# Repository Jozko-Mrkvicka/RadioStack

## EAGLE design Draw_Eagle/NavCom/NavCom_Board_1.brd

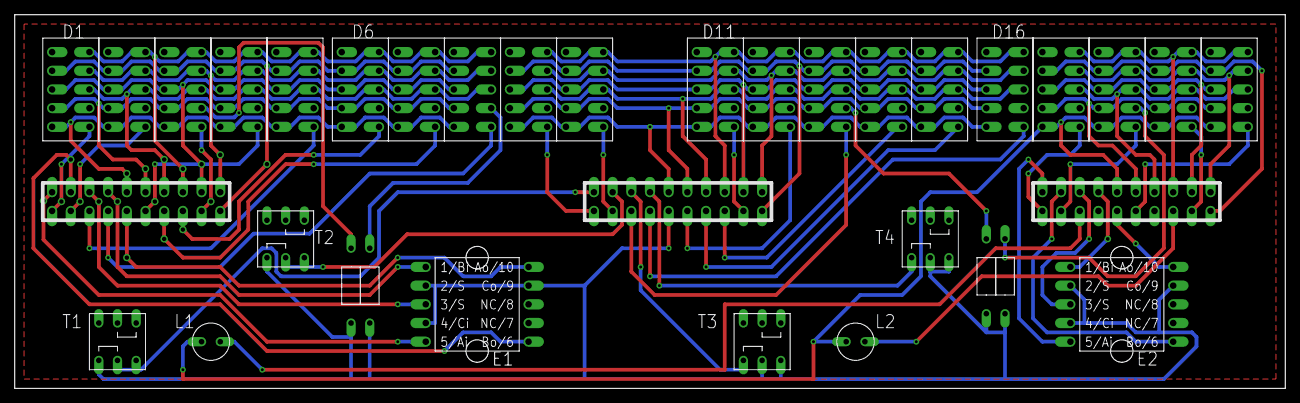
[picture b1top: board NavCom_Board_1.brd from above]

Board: 2 copper layers, 172.7 x 50.8 mm, 35 parts (0 on the bottom side), 62 nets.

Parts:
D1, D2, D3, D4, D5, D6, D7, D8, D9, D10, D11, D12, D13, D14, D15, D16, D17, D18, D19, D20: SA3611EWA
E37#1, E37#2: ELMA_E37
KON4, KON5, KON6: LISTA_2X10
LED1, LED2: LED_5MM
T1, T2, T3, T4: P1-0S
U$1, U$2, U$3, U$4: REZISTOR

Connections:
D1: D1.6, KON4.1
D2: D2.6, KON4.2
D3: D3.6, KON4.9
D4: D4.6, KON4.6
D5: D5.6, KON4.3
D6: D6.6, KON4.8
D7: D7.6, KON4.7
D8: D8.6, KON4.4
D9: D9.6, KON5.1
D10: D10.6, KON5.2
D11: D11.6, KON5.9
D12: D12.6, KON5.6
D13: D13.6, KON5.3
D14: D14.6, KON5.8
D15: D15.6, KON5.7
D16: D16.6, KON5.4
D17: D17.6, KON6.1
D18: D18.6, KON6.2
D19: D19.6, KON6.9
D20: D20.6, KON6.6
DRIVER1_SEG2: D1.2, D2.2, D3.2, D4.2, D5.2, D6.2, D7.2, D8.2, KON4.10
DRIVER1_SEG3: D1.3, D2.3, D3.3, D4.3, D5.3, D6.3, D7.3, D8.3, KON4.12
DRIVER1_SEG4: D1.4, D2.4, D3.4, D4.4, D5.4, D6.4, D7.4, D8.4, KON4.15
DRIVER1_SEG5: D1.5, D2.5, D3.5, D4.5, D5.5, D6.5, D7.5, D8.5, KON4.16
DRIVER1_SEG8: D1.8, D2.8, D3.8, D4.8, D5.8, D6.8, D7.8, D8.8, KON4.14
DRIVER1_SEG9: D1.9, D2.9, D3.9, D4.9, D5.9, D6.9, D7.9, D8.9, KON4.11
DRIVER1_SEG10: D1.10, D2.10, D3.10, D4.10, D5.10, D6.10, D7.10, D8.10, KON4.13
DRIVER2_SEG2: D9.2, D10.2, D11.2, D12.2, D13.2, D14.2, D15.2, D16.2, KON5.10
DRIVER2_SEG3: D9.3, D10.3, D11.3, D12.3, D13.3, D14.3, D15.3, D16.3, KON5.12
DRIVER2_SEG4: D9.4, D10.4, D11.4, D12.4, D13.4, D14.4, D15.4, D16.4, KON5.15
DRIVER2_SEG5: D9.5, D10.5, D11.5, D12.5, D13.5, D14.5, D15.5, D16.5, KON5.16
DRIVER2_SEG8: D9.8, D10.8, D11.8, D12.8, D13.8, D14.8, D15.8, D16.8, KON5.14
DRIVER2_SEG9: D9.9, D10.9, D11.9, D12.9, D13.9, D14.9, D15.9, D16.9, KON5.11
DRIVER2_SEG10: D9.10, D10.10, D11.10, D12.10, D13.10, D14.10, D15.10, D16.10, KON5.13
DRIVER3_SEG2: D17.2, D18.2, D19.2, D20.2, KON6.10
DRIVER3_SEG3: D17.3, D18.3, D19.3, D20.3, KON6.12
DRIVER3_SEG4: D17.4, D18.4, D19.4, D20.4, KON6.15
DRIVER3_SEG5: D17.5, D18.5, D19.5, D20.5, KON6.16, LED1.P$2, LED2.P$2
DRIVER3_SEG8: D17.8, D18.8, D19.8, D20.8, KON6.14
DRIVER3_SEG9: D17.9, D18.9, D19.9, D20.9, KON6.11
DRIVER3_SEG10: D17.10, D18.10, D19.10, D20.10, KON6.13
E37#1_1: E37#1.1, KON4.17
E37#1_3: E37#1.3, KON4.18
E37#1_5: E37#1.5, KON4.20
E37#1_6: E37#1.6, KON4.19
E37#1_10: E37#1.10, KON4.5
E37#2_1: E37#2.1, KON6.17
E37#2_3: E37#2.3, KON6.18
E37#2_5: E37#2.5, KON6.20
E37#2_6: E37#2.6, KON6.19
E37#2_10: E37#2.10, KON6.5
GND: E37#1.2, E37#1.4, E37#1.9, E37#2.2, E37#2.4, E37#2.9, KON5.5, T1.4, T2.4, T3.5, T3.6, T4.5, T4.6, U$1.P$1, U$2.P$1, U$3.P$1, U$4.P$1
LED1: KON6.3, LED1.P$1
LED2: KON6.8, LED2.P$1
unnamed: D3.7, U$4.P$2
unnamed: D18.7, U$2.P$2
unnamed: D13.7, U$1.P$2
unnamed: D8.7, U$3.P$2
T1: KON5.20, T1.5, T1.6
T2: KON5.19, T2.5, T2.6
T3: KON5.18, T3.4
T4: KON5.17, T4.4

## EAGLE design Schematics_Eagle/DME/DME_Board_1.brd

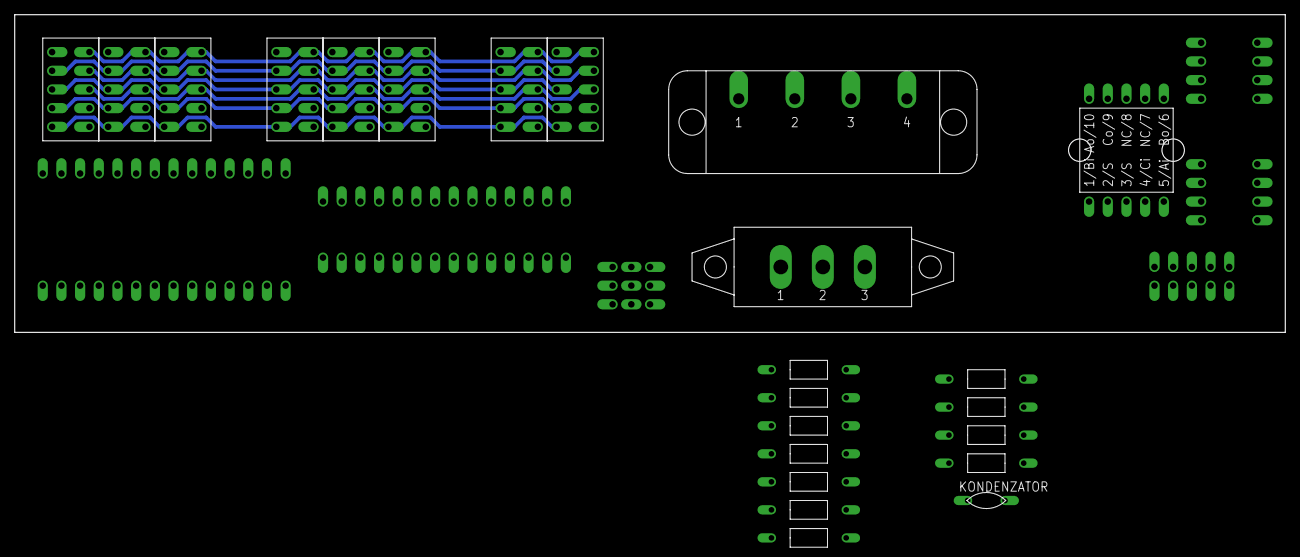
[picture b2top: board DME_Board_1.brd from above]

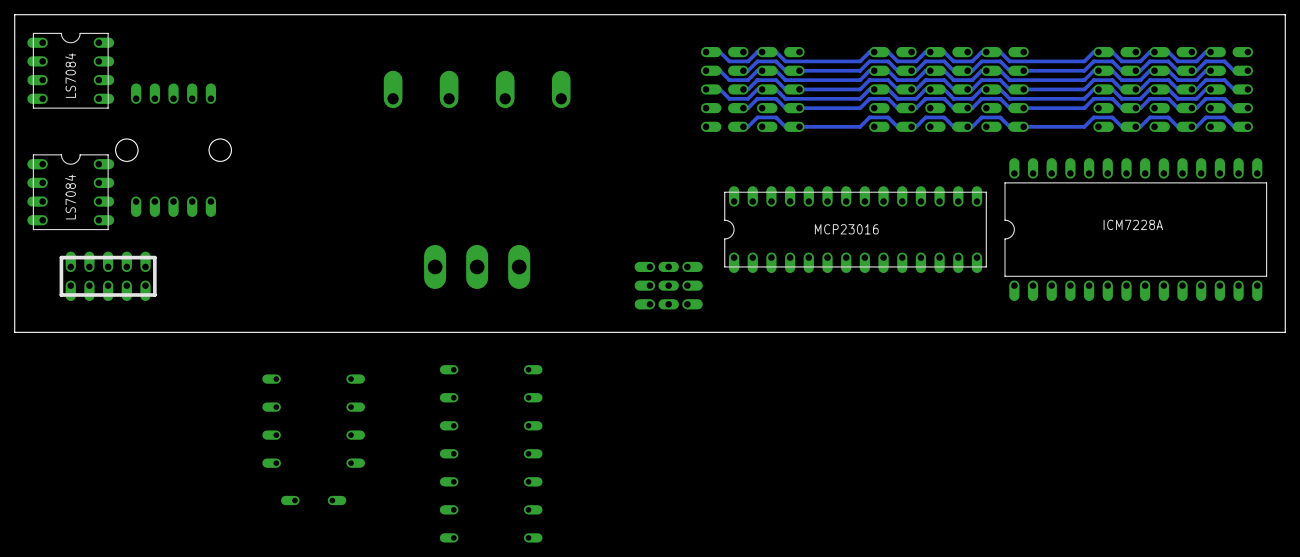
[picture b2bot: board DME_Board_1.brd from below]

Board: 2 copper layers, 172.7 x 43.2 mm, 29 parts (5 on the bottom side), 7 nets.

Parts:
U$1, U$2, U$3, U$4, U$5, U$6, U$7, U$8: SA3611EWA
U$9: ELMA_E37
U$10: 46311LD
U$11, U$13, U$15, U$19, U$25, U$26, U$27, U$28, U$29, U$30, U$31: REZISTOR
U$12: T220
U$14: ICM7228A
U$16: MCP23016
U$17: LISTA_2X5
U$21, U$22: LS7084
U$23: KONDENZATOR
U$24: ADRESA_0..2

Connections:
unnamed: U$1.10, U$2.10, U$3.10, U$4.10, U$5.10, U$6.10, U$7.10, U$8.10
unnamed: U$1.9, U$2.9, U$3.9, U$4.9, U$5.9, U$6.9, U$7.9, U$8.9
unnamed: U$1.8, U$2.8, U$3.8, U$4.8, U$5.8, U$6.8, U$7.8, U$8.8
unnamed: U$1.5, U$2.5, U$3.5, U$4.5, U$5.5, U$6.5, U$7.5, U$8.5
unnamed: U$1.2, U$2.2, U$3.2, U$4.2, U$5.2, U$6.2, U$7.2, U$8.2
unnamed: U$1.3, U$2.3, U$3.3, U$4.3, U$5.3, U$6.3, U$7.3, U$8.3
unnamed: U$1.4, U$2.4, U$3.4, U$4.4, U$5.4, U$6.4, U$7.4, U$8.4

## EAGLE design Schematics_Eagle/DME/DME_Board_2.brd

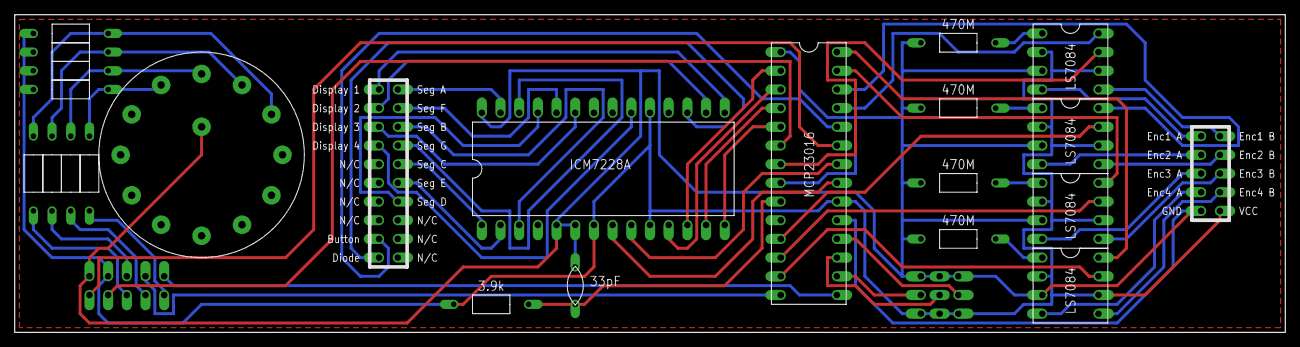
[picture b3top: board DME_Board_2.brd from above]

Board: 2 copper layers, 172.7 x 43.2 mm, 25 parts (1 on the bottom side), 57 nets.

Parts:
U$1, U$2, U$3, U$4: LS7084
U$5, U$27: LISTA_2X5
U$6: ICM7228A
U$7: LISTA_2X10
U$8, U$10, U$12, U$13: 470M; REZISTOR
U$9: MCP23016
U$11: ADRESA_0..2
U$14: 3.9k; REZISTOR
U$15: 33pF; KONDENZATOR
U$16: ROTARY_SWITCH
U$17, U$18, U$19, U$20, U$21, U$22, U$23, U$24: REZISTOR

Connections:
GND: U$1.P$3, U$2.P$3, U$3.P$3, U$4.P$3, U$5.1, U$6.P$5, U$6.P$6, U$6.P$28, U$8.P$1, U$9.VSS1, U$9.VSS2, U$9.VSS3, U$10.P$1, U$11.P$3, U$11.P$4, U$11.P$9, U$12.P$1, U$13.P$1, U$15.P$2, U$16.A, U$27.5
unnamed: U$6.P$27, U$7.20
unnamed: U$6.P$24, U$7.19
unnamed: U$6.P$3, U$7.18
unnamed: U$6.P$26, U$7.17
unnamed: U$6.P$1, U$7.16
unnamed: U$6.P$2, U$7.15
unnamed: U$6.P$25, U$7.14
unnamed: U$6.P$15, U$7.1
unnamed: U$6.P$16, U$7.2
unnamed: U$6.P$23, U$7.3
unnamed: U$6.P$20, U$7.4
unnamed: U$1.P$2, U$1.P$6, U$2.P$2, U$2.P$6, U$3.P$2, U$3.P$6, U$4.P$2, U$4.P$6, U$5.2, U$6.P$7, U$6.P$10, U$6.P$19, U$9.VDD, U$11.P$1, U$11.P$6, U$11.P$7, U$14.P$1, U$17.P$1, U$18.P$1, U$19.P$1, U$20.P$1, U$27.6
unnamed: U$6.P$12, U$9.GP1.0
unnamed: U$1.P$8, U$9.GP0.4
unnamed: U$2.P$8, U$9.GP0.5
unnamed: U$1.P$1, U$8.P$2
unnamed: U$2.P$1, U$10.P$2
unnamed: U$3.P$1, U$12.P$2
unnamed: U$4.P$1, U$13.P$2
unnamed: U$6.P$11, U$9.GP1.1
unnamed: U$3.P$8, U$9.GP0.6
unnamed: U$4.P$8, U$9.GP0.7
unnamed: U$1.P$7, U$9.GP1.4
unnamed: U$1.P$4, U$27.1
unnamed: U$1.P$5, U$27.10
unnamed: U$2.P$4, U$27.2
unnamed: U$2.P$5, U$27.9
unnamed: U$3.P$4, U$27.3
unnamed: U$3.P$5, U$27.8
unnamed: U$4.P$4, U$27.4
unnamed: U$4.P$5, U$27.7
unnamed: U$2.P$7, U$9.GP1.5
unnamed: U$3.P$7, U$9.GP1.6
unnamed: U$4.P$7, U$9.GP1.7
unnamed: U$9.A0, U$11.P$8
unnamed: U$9.A1, U$11.P$5
unnamed: U$9.A2, U$11.P$2
unnamed: U$6.P$13, U$9.GP1.2
unnamed: U$6.P$14, U$9.GP1.3
unnamed: U$16.11, U$17.P$2, U$21.P$2
unnamed: U$6.P$8, U$9.GP0.0
unnamed: U$6.P$9, U$9.GP0.1
unnamed: U$16.12, U$18.P$2, U$22.P$2
unnamed: U$5.4, U$9.SCL
unnamed: U$5.5, U$9.SDA
unnamed: U$5.9, U$9.~INT
unnamed: U$5.10, U$9.GP0.2
unnamed: U$9.CLK, U$14.P$2, U$15.P$1
unnamed: U$7.9, U$9.GP0.3
unnamed: U$6.P$17, U$7.10
unnamed: U$16.1, U$19.P$2, U$23.P$2
unnamed: U$16.2, U$20.P$2, U$24.P$2
unnamed: U$5.8, U$24.P$1
unnamed: U$5.3, U$23.P$1
unnamed: U$5.7, U$22.P$1
unnamed: U$5.6, U$21.P$1

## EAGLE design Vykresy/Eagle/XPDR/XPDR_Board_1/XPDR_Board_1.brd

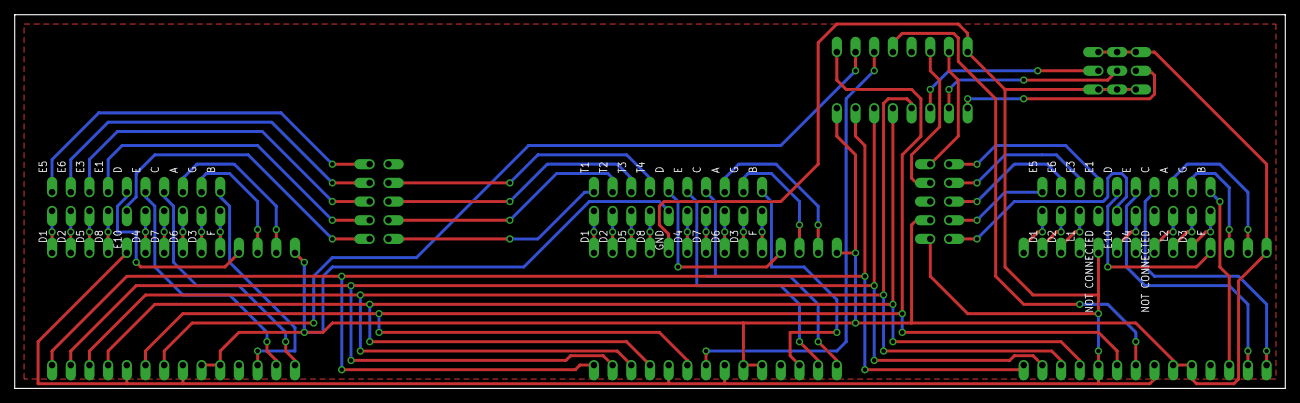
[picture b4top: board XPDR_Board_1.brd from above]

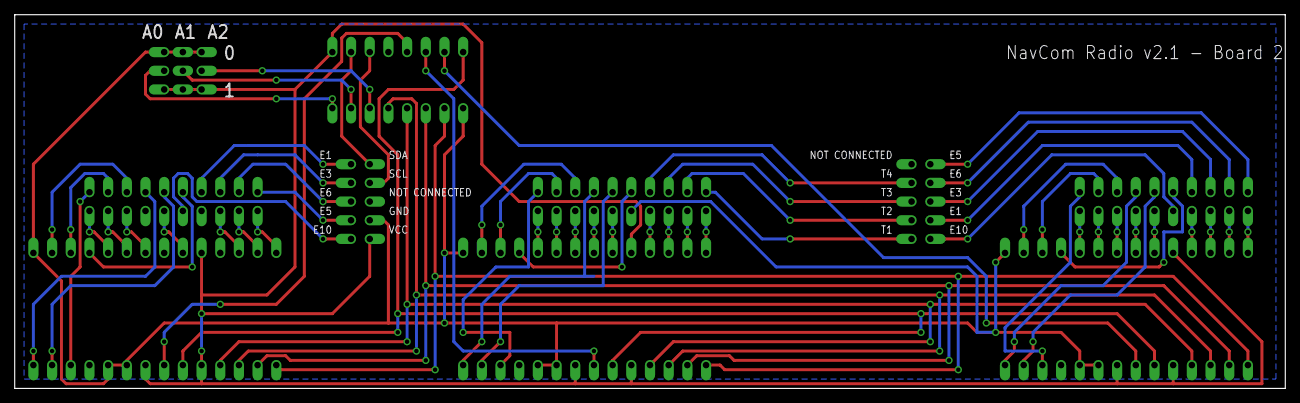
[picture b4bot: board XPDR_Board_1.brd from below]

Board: 2 copper layers, 172.7 x 50.8 mm, 10 parts (4 on the bottom side), 72 nets.

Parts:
U$1, U$2, U$3: LISTA_2X10
U$4, U$5, U$6: ICM7228A
U$7, U$27: LISTA_2X5
U$9: PCF8574A
U$11: ADRESA_0..2

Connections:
GND: U$2.5, U$4.P$5, U$4.P$6, U$4.P$28, U$5.P$5, U$5.P$6, U$5.P$28, U$6.P$5, U$6.P$6, U$6.P$28, U$9.VSS, U$11.P$3, U$11.P$4, U$11.P$9, U$27.4
unnamed: U$1.1, U$4.P$15
unnamed: U$2.1, U$5.P$15
unnamed: U$1.2, U$4.P$16
unnamed: U$1.3, U$4.P$17
unnamed: U$1.4, U$4.P$18
unnamed: U$1.11, U$4.P$3
unnamed: U$1.6, U$4.P$20
unnamed: U$1.7, U$4.P$21
unnamed: U$1.8, U$4.P$22
unnamed: U$1.9, U$4.P$23
unnamed: U$1.10, U$4.P$24
unnamed: U$1.12, U$4.P$26
unnamed: U$1.13, U$4.P$27
unnamed: U$2.2, U$5.P$16
unnamed: U$2.3, U$5.P$17
unnamed: U$2.4, U$5.P$18
unnamed: U$3.1, U$6.P$15
unnamed: U$2.6, U$5.P$20
unnamed: U$2.7, U$5.P$21
unnamed: U$2.8, U$5.P$22
unnamed: U$2.9, U$5.P$23
unnamed: U$2.10, U$5.P$24
unnamed: U$3.2, U$6.P$16
unnamed: U$3.3, U$6.P$17
unnamed: U$3.6, U$6.P$20
unnamed: U$3.8, U$6.P$22
unnamed: U$3.9, U$6.P$23
unnamed: U$3.10, U$6.P$24
unnamed: U$2.16, U$5.P$25
unnamed: U$2.12, U$5.P$26
unnamed: U$2.13, U$5.P$27
unnamed: U$3.16, U$6.P$25
unnamed: U$3.12, U$6.P$26
unnamed: U$3.13, U$6.P$27
unnamed: U$1.14, U$4.P$1
unnamed: U$1.15, U$4.P$2
unnamed: U$1.16, U$4.P$25
unnamed: U$4.P$14, U$5.P$14, U$6.P$14, U$9.P3
unnamed: U$4.P$13, U$5.P$13, U$6.P$13, U$9.P2
unnamed: U$4.P$12, U$5.P$12, U$6.P$12, U$9.P0
unnamed: U$4.P$11, U$5.P$11, U$6.P$11, U$9.P1
unnamed: U$4.P$9, U$5.P$9, U$6.P$9, U$9.P4
unnamed: U$2.14, U$5.P$1
unnamed: U$2.15, U$5.P$2
unnamed: U$9.A0, U$11.P$2
unnamed: U$3.14, U$6.P$1
unnamed: U$3.15, U$6.P$2
unnamed: U$9.A1, U$11.P$5
unnamed: U$3.11, U$6.P$3
unnamed: U$2.11, U$5.P$3
unnamed: U$9.A2, U$11.P$8
unnamed: U$6.P$8, U$9.P7
unnamed: U$5.P$8, U$9.P6
unnamed: U$4.P$8, U$9.P5
unnamed: U$1.20, U$7.1
unnamed: U$4.P$7, U$4.P$10, U$4.P$19, U$5.P$7, U$5.P$10, U$5.P$19, U$6.P$7, U$6.P$10, U$6.P$19, U$9.VDD, U$11.P$1, U$11.P$6, U$11.P$7, U$27.5
unnamed: U$1.19, U$7.2
unnamed: U$1.18, U$7.3
unnamed: U$1.17, U$7.4
unnamed: U$1.5, U$7.5
unnamed: U$2.20, U$7.6
unnamed: U$2.19, U$7.7
unnamed: U$2.18, U$7.8
unnamed: U$2.17, U$7.9
unnamed: U$9.SDA, U$27.1
unnamed: U$9.SCL, U$27.2
unnamed: U$3.17, U$27.10
unnamed: U$3.18, U$27.9
unnamed: U$3.5, U$27.6
unnamed: U$3.19, U$27.8
unnamed: U$3.20, U$27.7
